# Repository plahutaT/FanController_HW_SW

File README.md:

# FanController PCB

A custom PCB for controlling fans in industrial electronic cabinets. It uses the PIC18F45K22 microcontroller and interfaces with two DS18B20 temperature sensors to regulate fan speed based on the temperature difference inside and outside the cabinet. It supports both 230V AC and 24V DC fans and has an option for logging data over TCP via an ESP01 module.

## Features

- Interfaces with two DS18B20 temperature sensors.
- Supports one 230V AC fan and one 24V DC fan.
- Regulates fan speed based on the temperature difference inside and outside the cabinet.
- Optional data logging over TCP using an ESP01 module.

## Hardware Components

- **Microcontroller**: PIC18F45K22
- **Temperature Sensors**: 2x DS18B20
- **Fan Support**:
  - 230V AC fan
  - 24V DC fan
- **Connectivity**: ESP01 module for optional data logging over TCP

### Prerequisites

- **MPLAB X IDE** for firmware development.
- **PICkit** or another compatible programmer for flashing the PIC18F45K22.
- PCB and components (refer to the Bill of Materials in the `/hardware` directory).

## Usage

Once powered on, the FanController PCB will:

- Read temperatures from the inside and outside DS18B20 sensors.
- Automatically adjust the speed of the connected 230V AC or 24V DC fan based on the temperature difference.
- Optionally, log temperature and fan speed data over TCP if the ESP01 module is connected and properly configured.

## License

This project is licensed under the MIT License. See the [LICENSE](LICENSE) file for details.

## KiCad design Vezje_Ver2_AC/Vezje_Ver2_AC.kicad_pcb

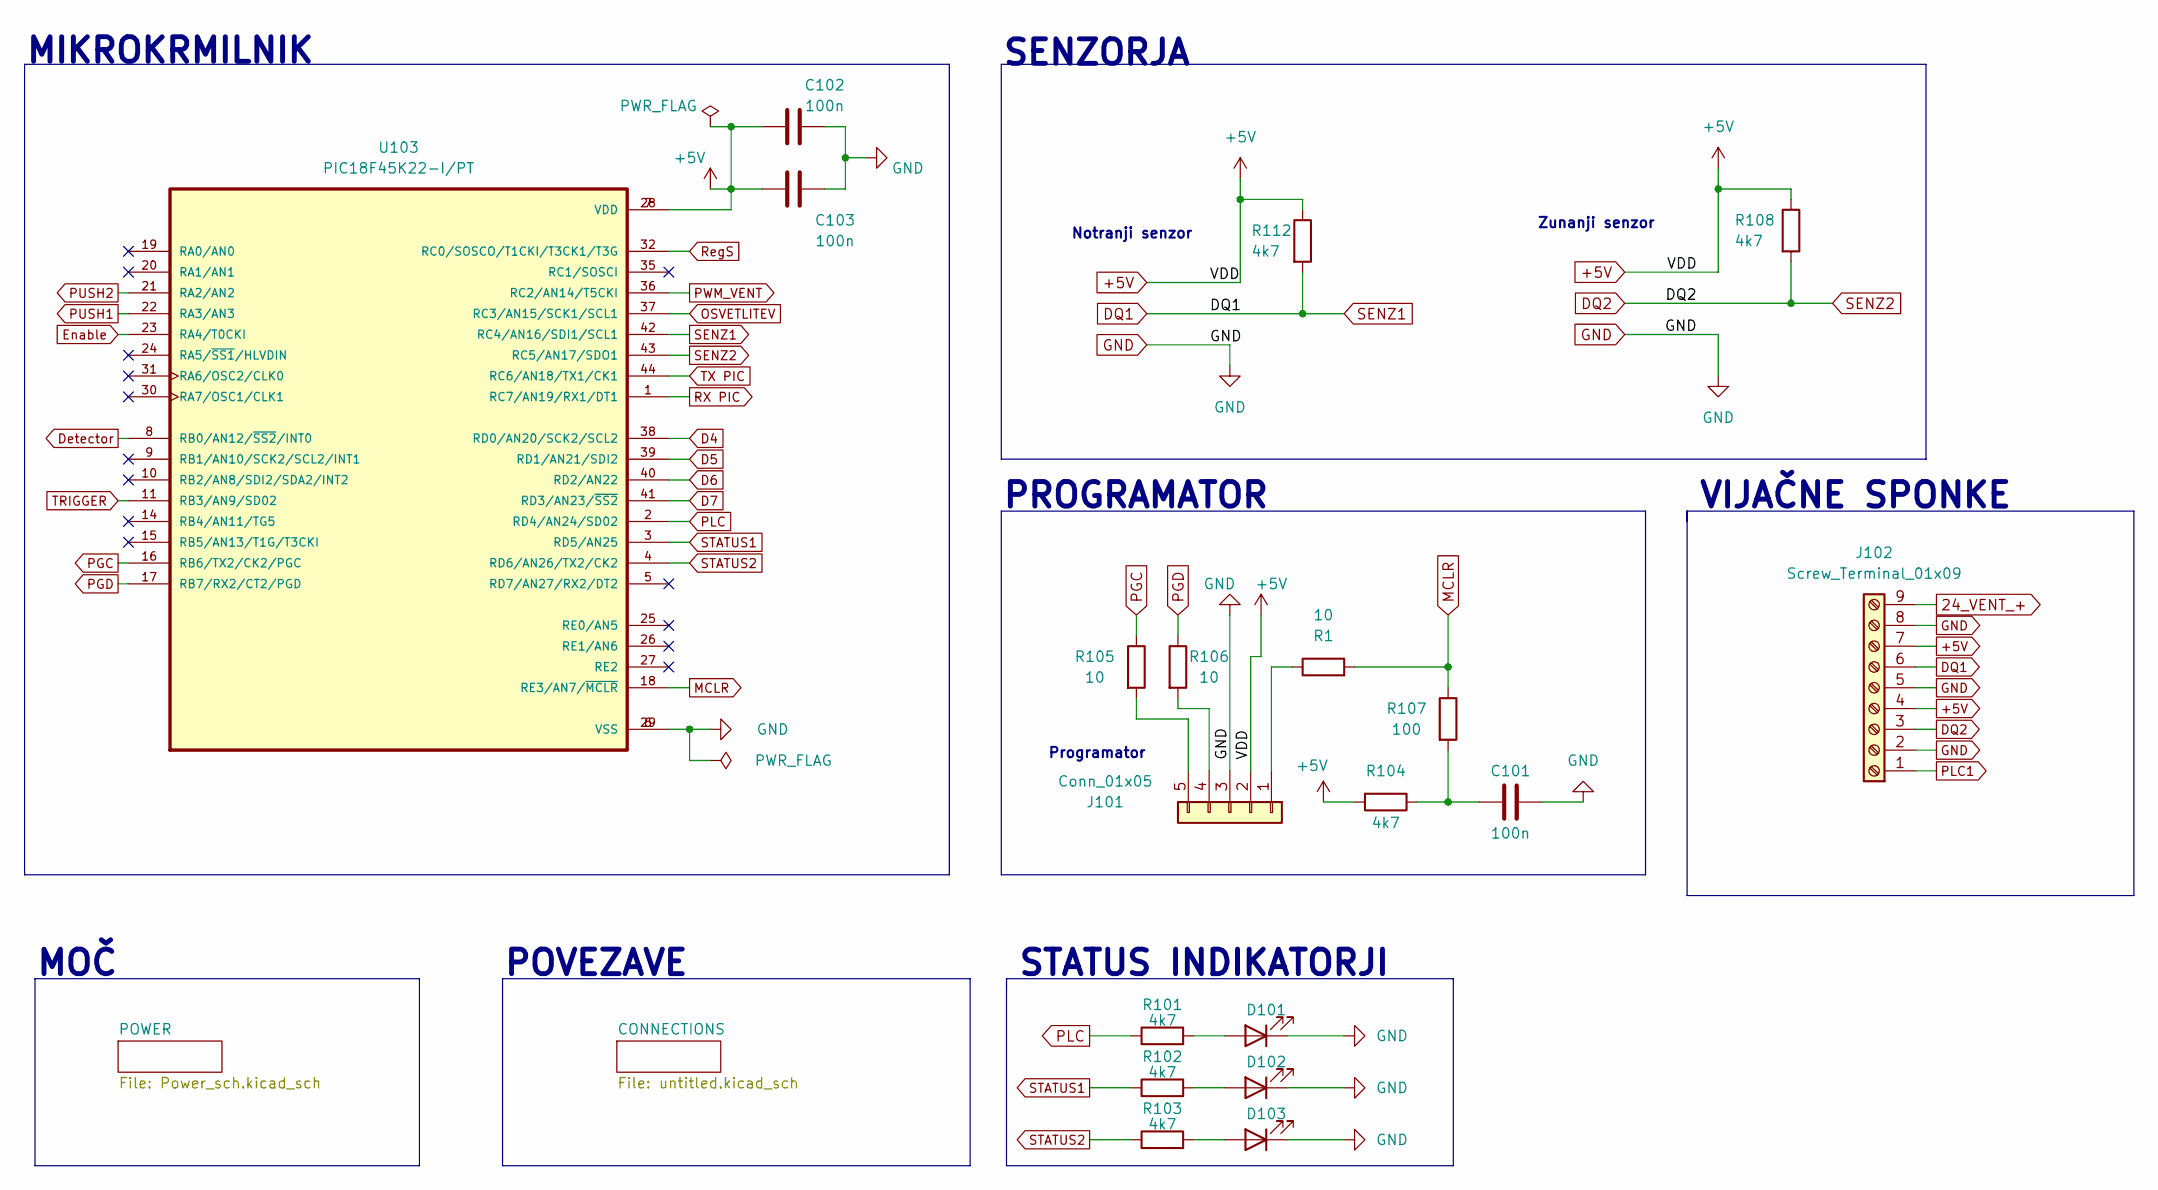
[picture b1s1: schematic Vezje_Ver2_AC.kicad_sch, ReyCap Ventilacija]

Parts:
C101, C102, C103: 100n; C_1206_3216Metric_Pad1.33x1.80mm_HandSolder
D101, D102, D103: LED; LED_1206_3216Metric_Pad1.42x1.75mm_HandSolder
J101: Conn_01x05; PinHeader_1x05_P2.54mm_Vertical
J102: Screw_Terminal_01x09; TerminalBlock_Phoenix_MKDS-1,5-9-5.08_1x09_P5.08mm_Horizont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
R1, R105, R106: 10; R_1206_3216Metric_Pad1.30x1.75mm_HandSolder
R101, R102, R103, R104, R108, R112: 4k7; R_1206_3216Metric_Pad1.30x1.75mm_HandSolder
R107: 100; R_1206_3216Metric_Pad1.30x1.75mm_HandSolder
U103: PIC18F45K22-I/PT; QFP80P1200X1200X120-44N

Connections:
24_VENT_+: J102.9; also elsewhere on the board
+5V: C102.1, C103.1, J101.2, J102.4, J102.7, R104.2, R108.1, R112.1, U103.7 (VDD), U103.28 (VDD); also elsewhere on the board
D4: U103.38 (RD0/AN20/SCK2/SCL2); also elsewhere on the board
D5: U103.39 (RD1/AN21/SDI2); also elsewhere on the board
D6: U103.40 (RD2/AN22); also elsewhere on the board
D7: U103.41 (RD3/AN23/~SS2); also elsewhere on the board
DQ1: J102.6, R112.2, U103.42 (RC4/AN16/SDI1/SCL1)
DQ2: J102.3, R108.2, U103.43 (RC5/AN17/SDO1)
Detector: U103.8 (RB0/AN12/~SS2/INT0); also elsewhere on the board
Enable: U103.23 (RA4/T0CKI); also elsewhere on the board
GND: C101.2, C102.2, C103.2, D101.1 (K), D102.1 (K), D103.1 (K), J101.3, J102.2, J102.5, J102.8, U103.6 (VSS), U103.29 (VSS); also elsewhere on the board
MCLR: R1.2, R107.1, U103.18 (RE3/AN7/~MCLR)
unnamed: C101.1, R104.1, R107.2
unnamed: D101.2 (A), R101.2
unnamed: D102.2 (A), R102.2
unnamed: D103.2 (A), R103.2
unnamed: J101.1, R1.1
unnamed: J101.4, R106.2
unnamed: J101.5, R105.2
OSVETLITEV: U103.37 (RC3/AN15/SCK1/SCL1); also elsewhere on the board
PGC: R105.1, U103.16 (RB6/TX2/CK2/PGC)
PGD: R106.1, U103.17 (RB7/RX2/CT2/PGD)
PLC: R101.1, U103.2 (RD4/AN24/SD02); also elsewhere on the board
PLC1: J102.1; also elsewhere on the board
PUSH1: U103.22 (RA3/AN3); also elsewhere on the board
PUSH2: U103.21 (RA2/AN2); also elsewhere on the board
PWM_VENT: U103.36 (RC2/AN14/T5CKI); also elsewhere on the board
RX PIC: U103.1 (RC7/AN19/RX1/DT1); also elsewhere on the board
RegS: U103.32 (RC0/SOSCO/T1CKI/T3CK1/T3G); also elsewhere on the board
STATUS1: R102.1, U103.3 (RD5/AN25)
STATUS2: R103.1, U103.4 (RD6/AN26/TX2/CK2)
TRIGGER: U103.11 (RB3/AN9/SD02); also elsewhere on the board
TX PIC: U103.44 (RC6/AN18/TX1/CK1); also elsewhere on the board

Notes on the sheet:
MOČ
Notranji senzor
VIJAČNE SPONKE
PROGRAMATOR
MIKROKRMILNIK
POVEZAVE
Programator
STATUS INDIKATORJI
SENZORJA
Zunanji senzor

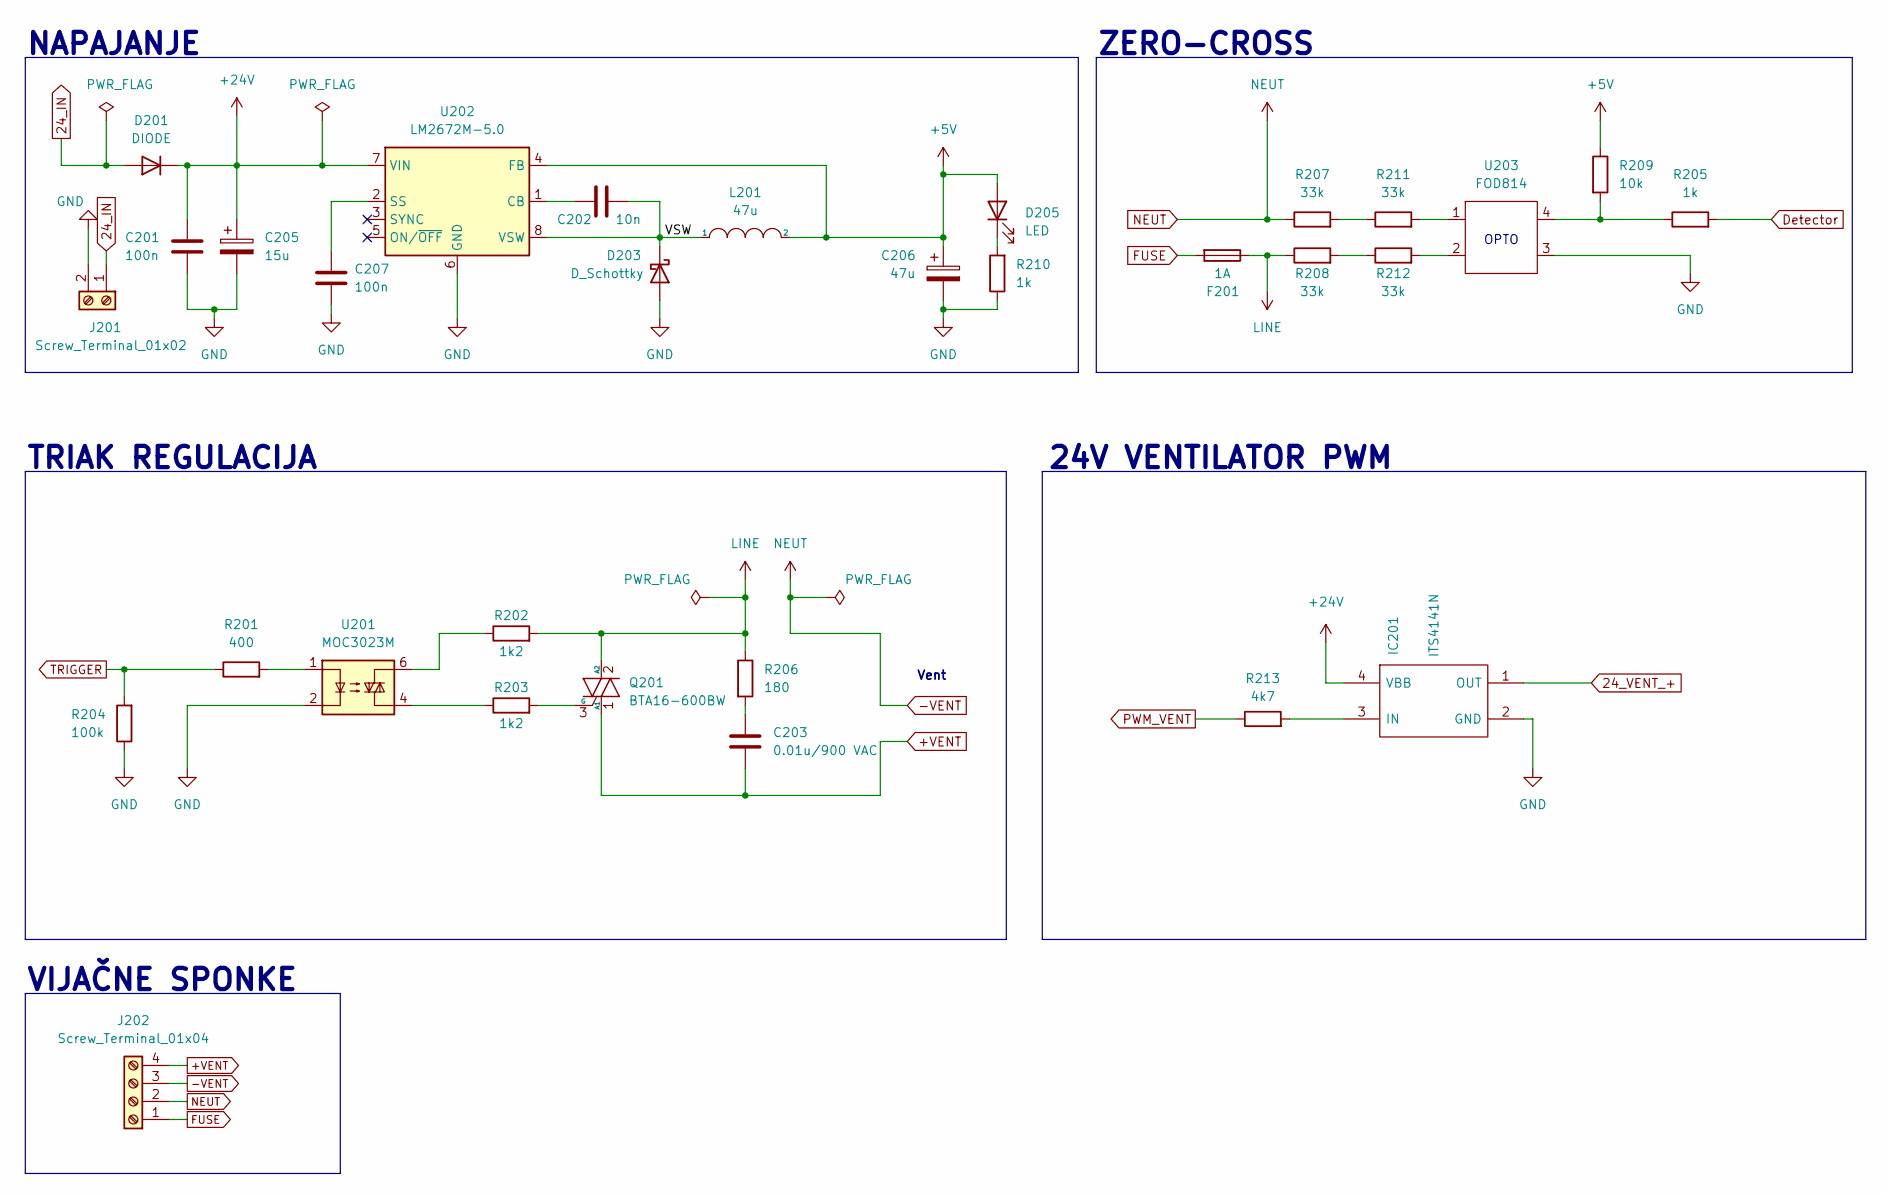
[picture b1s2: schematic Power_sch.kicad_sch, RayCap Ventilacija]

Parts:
C201, C207: 100n; C_1206_3216Metric_Pad1.33x1.80mm_HandSolder
C202: 10n; C_1206_3216Metric_Pad1.33x1.80mm_HandSolder
C203: 0.01u/900 VAC; C_Rect_L18.0mm_W5.0mm_P15.00mm_FKS3_FKP3
C205: 15u; CP_Elec_8x6.7
C206: 47u; CP_Elec_6.3x9.9
D201: DIODE; D_SMB
D203: D_Schottky; D_SMB
D205: LED; LED_1206_3216Metric_Pad1.42x1.75mm_HandSolder
F201: 1A; 696105003002
IC201: ITS4141N; SOT230P700X170-4N; Manufacturer_Part_Number ITS4141N; Mouser Part Number 726-ITS4141N
J201: Screw_Terminal_01x02; TerminalBlock_Phoenix_MKDS-1,5-2-5.08_1x02_P5.08mm_Horizont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
J202: Screw_Terminal_01x04; TerminalBlock_Phoenix_MKDS-1,5-4-5.08_1x04_P5.08mm_Horizont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
L201: 47u; L_7.3x7.3_H3.5
Q201: BTA16-600BW; TO-220-3_Vertical
R201: 400; R_1206_3216Metric_Pad1.30x1.75mm_HandSolder
R202, R203: 1k2; R_Axial_DIN0207_L6.3mm_D2.5mm_P10.16mm_Horizontal
R204: 100k; R_1206_3216Metric_Pad1.30x1.75mm_HandSolder
R205, R210: 1k; R_1206_3216Metric_Pad1.30x1.75mm_HandSolder
R206: 180; R_Axial_DIN0207_L6.3mm_D2.5mm_P10.16mm_Horizontal
R207, R208, R211, R212: 33k; R_1210_3225Metric_Pad1.30x2.65mm_HandSolder
R209: 10k; R_1206_3216Metric_Pad1.30x1.75mm_HandSolder
R213: 4k7; R_1206_3216Metric_Pad1.30x1.75mm_HandSolder
U201: MOC3023M; DIP-6_W7.62mm
U202: LM2672M-5.0; SOIC-8_3.9x4.9mm_P1.27mm
U203: FOD814; DIP762W50P254L510H440Q4

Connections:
24_IN: D201.2 (K), J201.1
24_VENT_+: IC201.1 (OUT); also elsewhere on the board
+5V: C206.1, D205.2 (A), L201.2, R209.1, U202.4 (FB); also elsewhere on the board
+24V: C201.1, C205.1, D201.1 (A), IC201.4 (VBB), U202.7 (VIN); also elsewhere on the board
+VENT: C203.2, J202.4, Q201.1 (A1)
-VENT: J202.2, J202.3, R207.1
/POWER/VSW: C202.2, D203.1 (K), L201.1, U202.8 (VSW)
Detector: R205.2; also elsewhere on the board
FUSE: F201.2, J202.1
GND: C201.2, C205.2, C206.2, C207.2, D203.2 (A), IC201.2 (GND), J201.2, R204.1, R210.1, U201.2, U202.6 (GND), U203.3; also elsewhere on the board
LINE: F201.1, Q201.2 (A2), R202.2, R206.1, R208.1
unnamed: C202.1, U202.1 (CB)
unnamed: C203.1, R206.2
unnamed: C207.1, U202.2 (SS)
unnamed: D205.1 (K), R210.2
unnamed: IC201.3 (IN), R213.2
unnamed: Q201.3 (G), R203.2
unnamed: R201.2, U201.1
unnamed: R202.1, U201.6
unnamed: R203.1, U201.4
unnamed: R205.1, R209.2, U203.4
unnamed: R207.2, R211.1
unnamed: R208.2, R212.1
unnamed: R211.2, U203.1
unnamed: R212.2, U203.2
PWM_VENT: R213.1; also elsewhere on the board
TRIGGER: R201.1, R204.2; also elsewhere on the board

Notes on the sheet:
24V VENTILATOR PWM
OPTO
NAPAJANJE
VIJAČNE SPONKE
Vent
ZERO-CROSS
TRIAK REGULACIJA

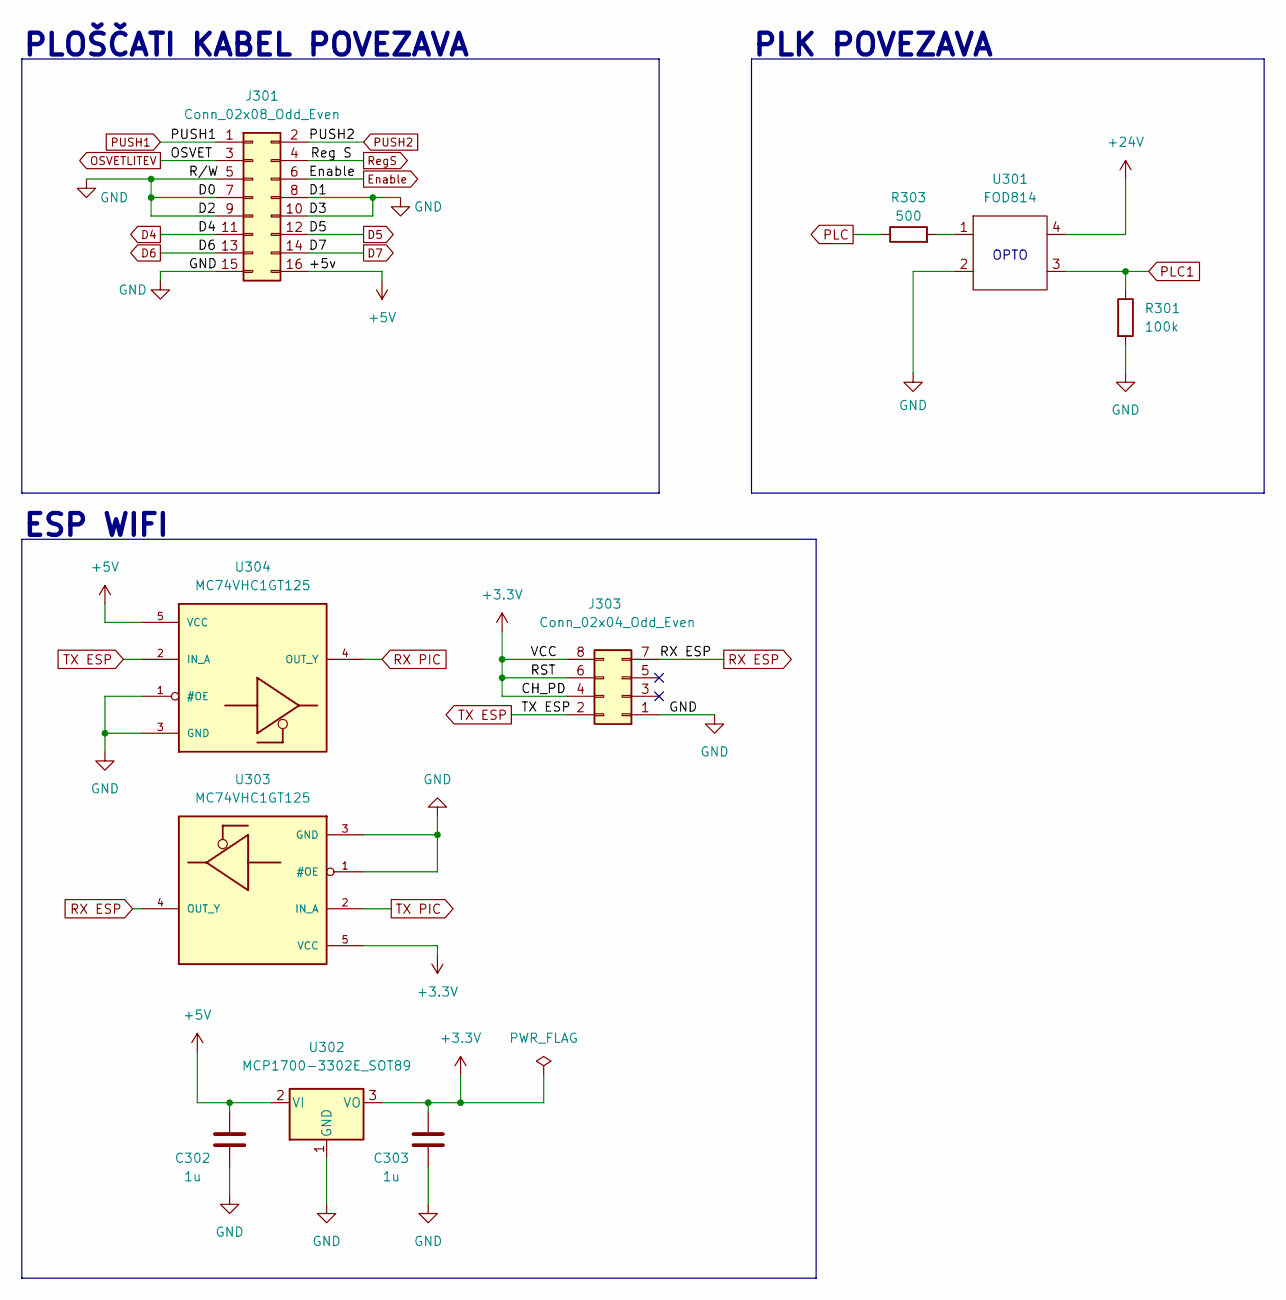
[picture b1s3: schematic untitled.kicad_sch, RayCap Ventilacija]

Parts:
C302, C303: 1u; C_1206_3216Metric_Pad1.33x1.80mm_HandSolder
J301: Conn_02x08_Odd_Even; PinSocket_2x08_P2.54mm_Vertical
J303: Conn_02x04_Odd_Even; PinSocket_2x04_P2.54mm_Vertical
R301: 100k; R_1206_3216Metric_Pad1.30x1.75mm_HandSolder
R303: 500; R_1206_3216Metric_Pad1.30x1.75mm_HandSolder
U301: FOD814; DIP762W50P254L510H440Q4
U302: MCP1700-3302E_SOT89; SOT-89-3_Handsoldering
U303, U304: MC74VHC1GT125; SOT23-5

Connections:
+3.3V: C303.2, J303.4, J303.6, J303.8, U302.3 (VO), U303.5 (VCC)
+5V: C302.2, J301.16, U302.2 (VI), U304.5 (VCC); also elsewhere on the board
+24V: U301.4; also elsewhere on the board
D4: J301.11; also elsewhere on the board
D5: J301.12; also elsewhere on the board
D6: J301.13; also elsewhere on the board
D7: J301.14; also elsewhere on the board
Enable: J301.6; also elsewhere on the board
GND: C302.1, C303.1, J301.5, J301.7, J301.8, J301.9, J301.10, J301.15, J303.1, R301.2, U301.2, U302.1 (GND), U303.1 (#OE), U303.3 (GND), U304.1 (#OE), U304.3 (GND); also elsewhere on the board
unnamed: R303.2, U301.1
OSVETLITEV: J301.3; also elsewhere on the board
PLC: R303.1; also elsewhere on the board
PLC1: R301.1, U301.3; also elsewhere on the board
PUSH1: J301.1; also elsewhere on the board
PUSH2: J301.2; also elsewhere on the board
RX ESP: J303.7, U303.4 (OUT_Y)
RX PIC: U304.4 (OUT_Y); also elsewhere on the board
RegS: J301.4; also elsewhere on the board
TX ESP: J303.2, U304.2 (IN_A)
TX PIC: U303.2 (IN_A); also elsewhere on the board

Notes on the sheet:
ESP WIFI
PLK POVEZAVA
OPTO
PLOŠČATI KABEL POVEZAVA

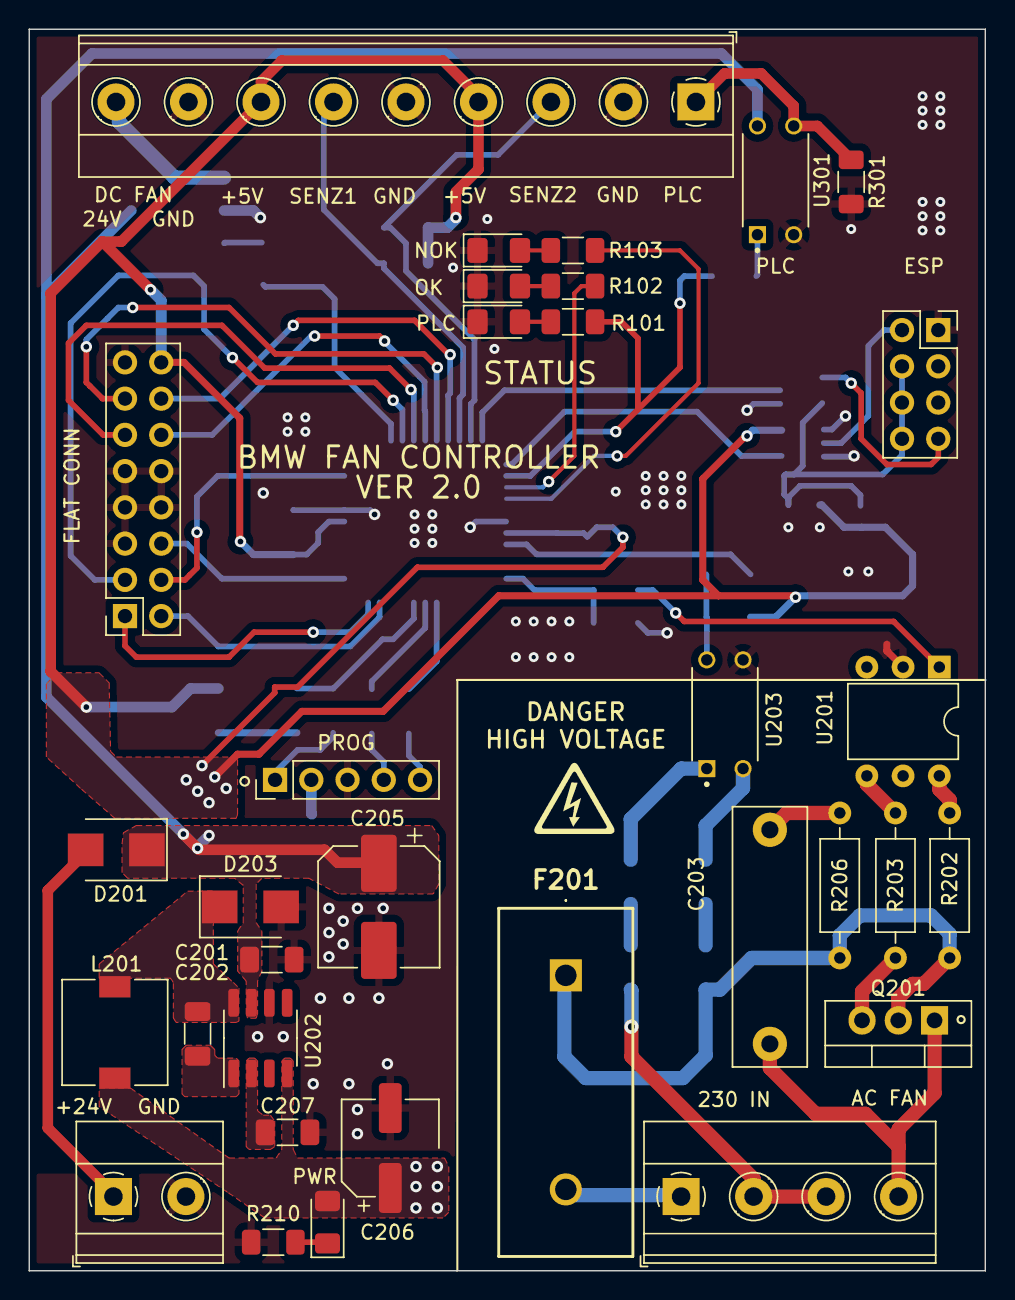
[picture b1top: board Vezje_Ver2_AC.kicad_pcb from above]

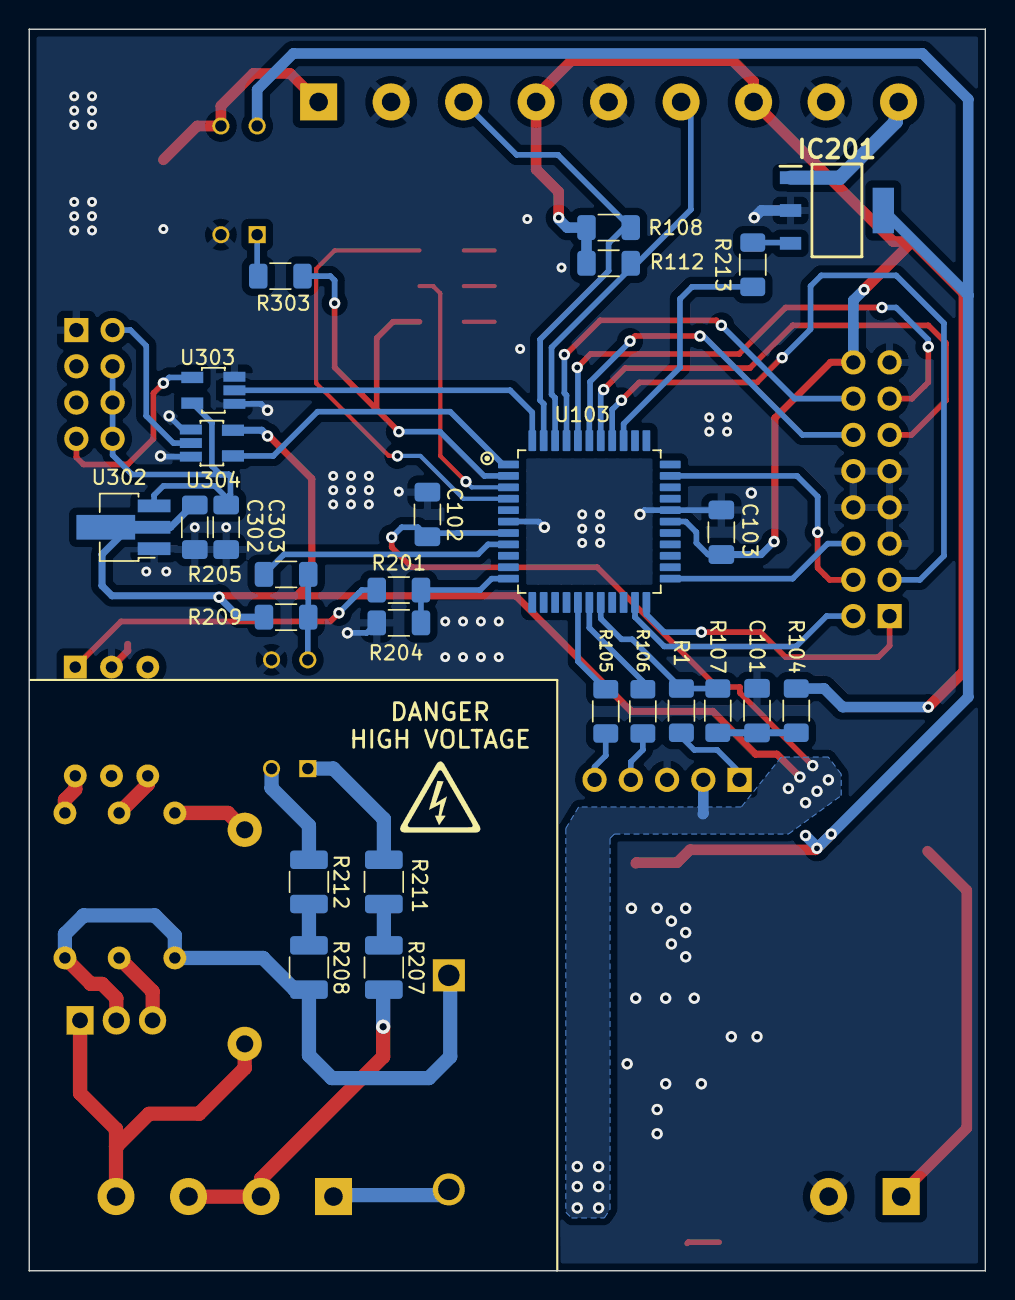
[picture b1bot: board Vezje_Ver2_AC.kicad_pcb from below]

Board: 2 copper layers, 67.0 x 87.0 mm, 60 parts (27 on the bottom side), 58 nets.
